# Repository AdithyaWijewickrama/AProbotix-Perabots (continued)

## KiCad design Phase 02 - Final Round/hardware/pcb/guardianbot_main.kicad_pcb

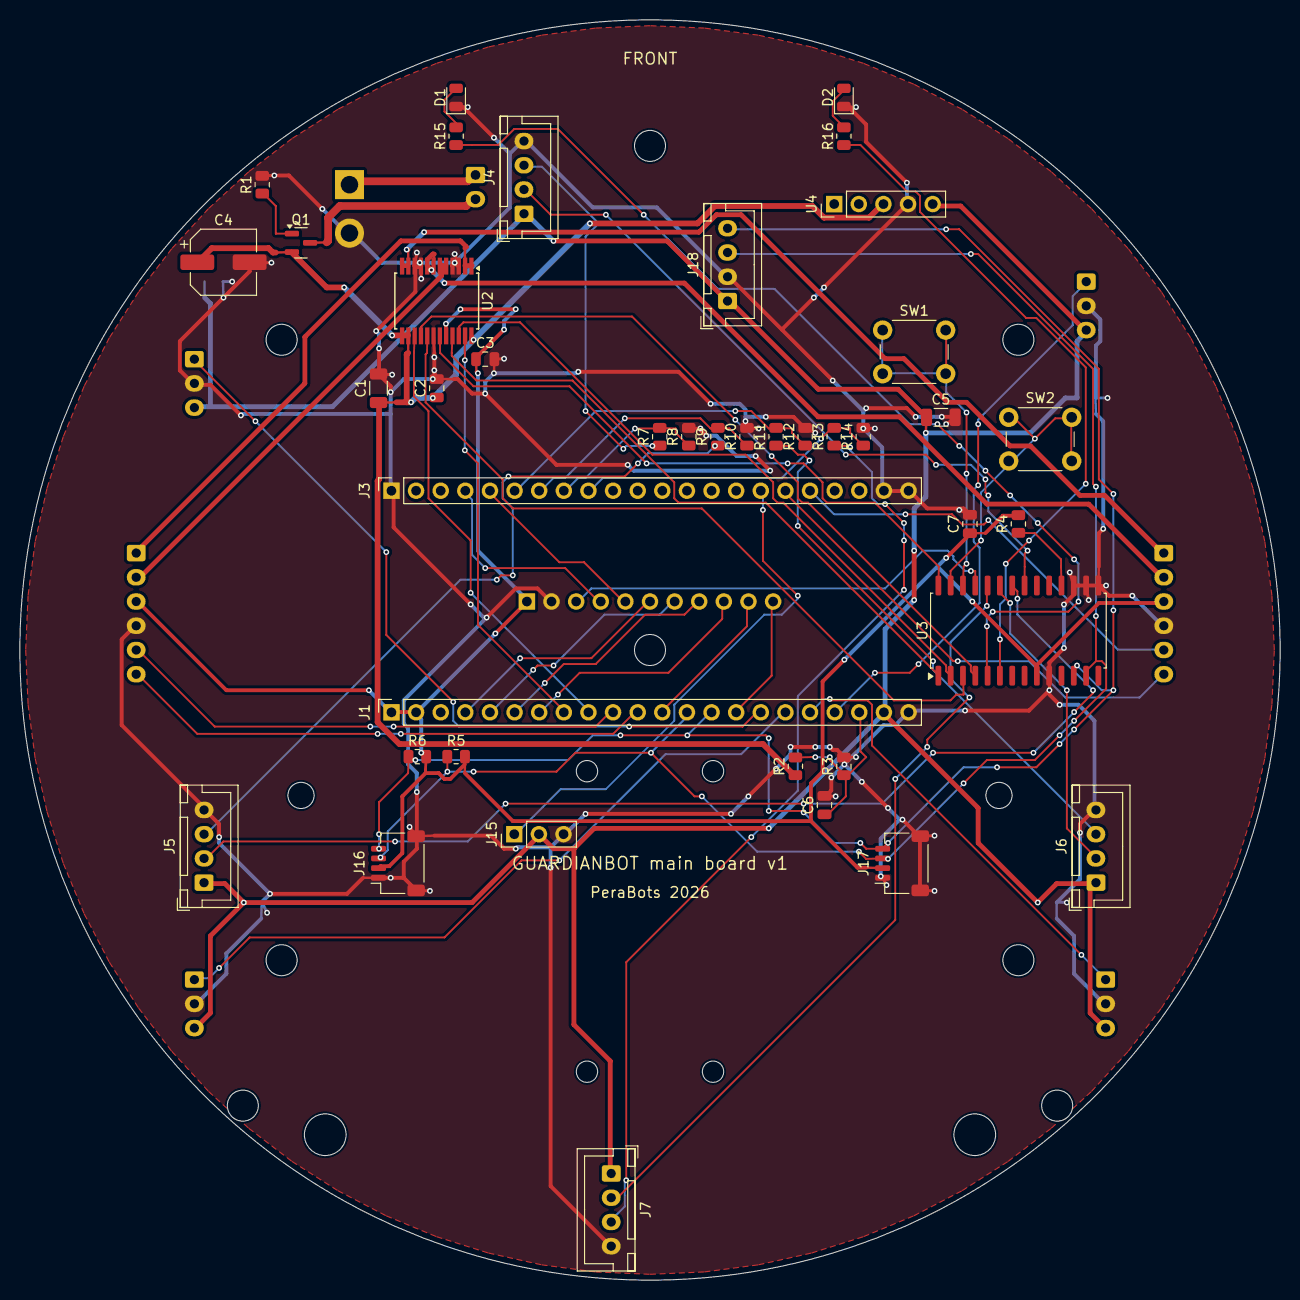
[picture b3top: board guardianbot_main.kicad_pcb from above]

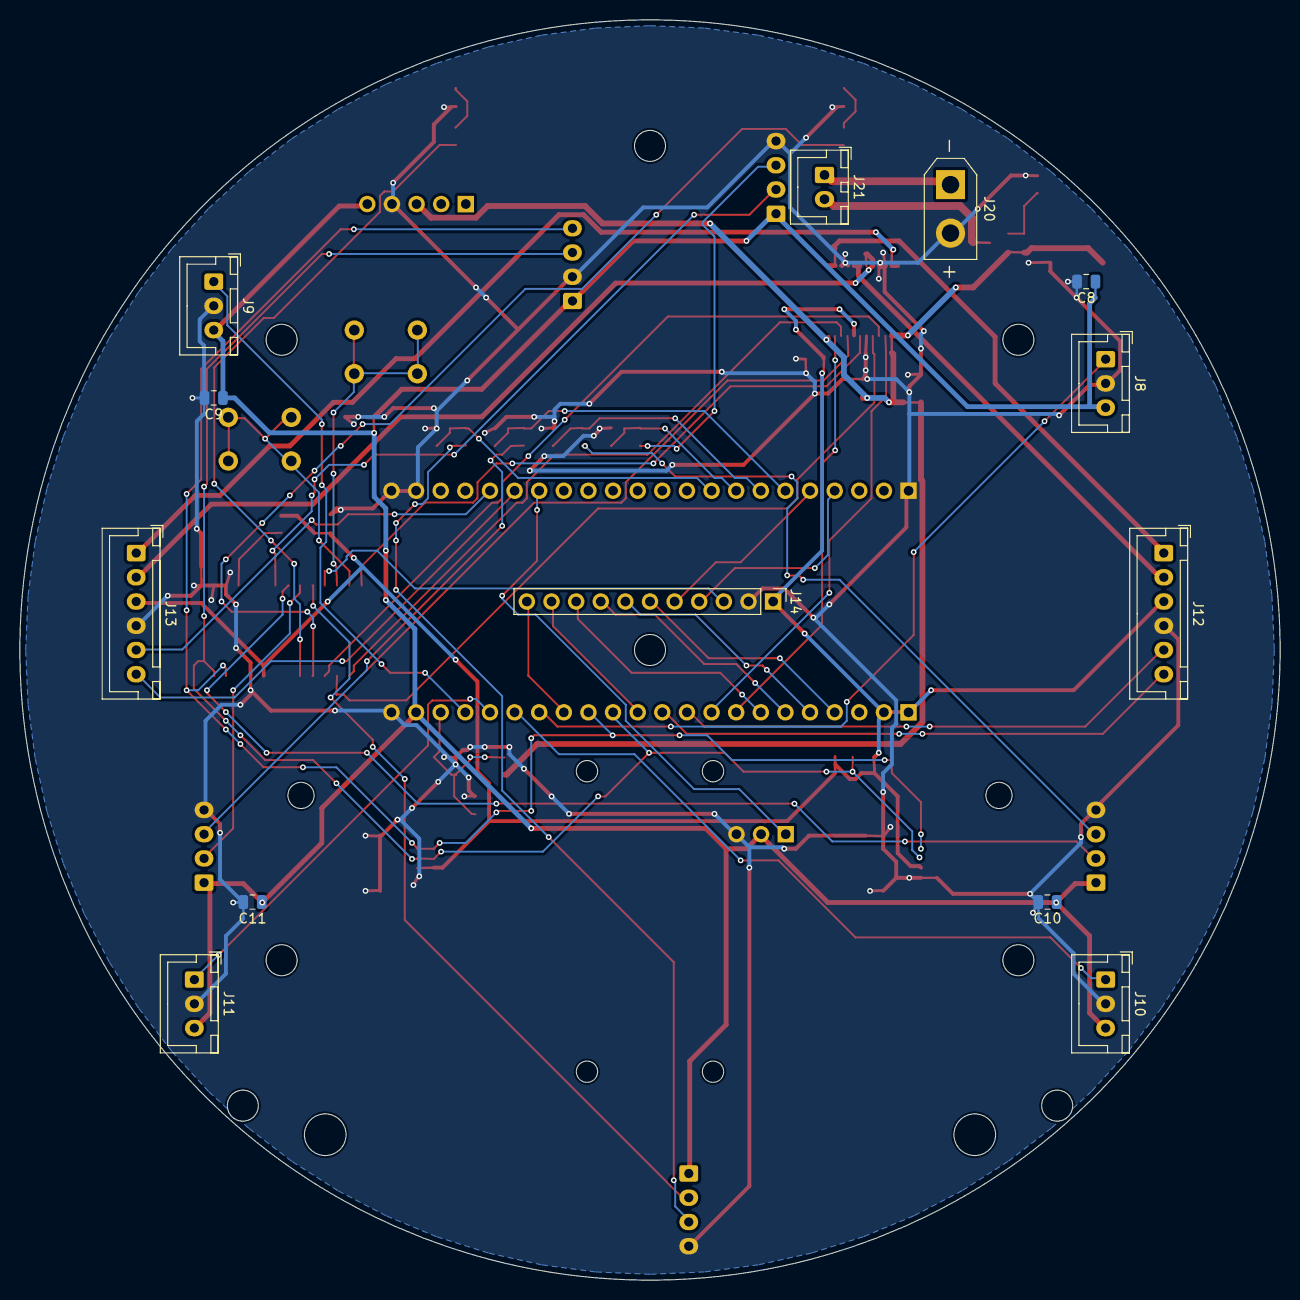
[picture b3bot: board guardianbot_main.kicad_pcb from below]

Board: 2 copper layers, 130.0 x 130.0 mm, 70 parts (13 on the bottom side), 58 nets.

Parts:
C1: 10uF 25V; C_1206_3216Metric
C2, C3, C6, C7: 100nF; C_0805_2012Metric
C4: 220uF 16V; CP_Elec_6.3x7.7
C5: 47uF 10V; C_1206_3216Metric
C8, C9, C10, C11: 10uF; C_0805_2012Metric
D1: BLUE; LED_0805_2012Metric
D2: GREEN; LED_0805_2012Metric
H1, H2, H3, H4, H5, H6, H7, H8: MountingHole_3.2mm_M3
H9, H10: MountingHole_4.3mm_M4
H11, H12: MountingHole_2.7mm_M2.5
H13, H14, H15, H16: MountingHole_2.2mm_M2
J1: DevKitC J1; PinSocket_1x22_P2.54mm_Vertical
J3: DevKitC J3; PinSocket_1x22_P2.54mm_Vertical
J4: US front; JST_XH_B4B-XH-A_1x04_P2.50mm_Vertical
J5: US left; JST_XH_B4B-XH-A_1x04_P2.50mm_Vertical
J6: US right; JST_XH_B4B-XH-A_1x04_P2.50mm_Vertical
J7: US back; JST_XH_B4B-XH-A_1x04_P2.50mm_Vertical
J8: IR front-left; JST_XH_B3B-XH-A_1x03_P2.50mm_Vertical
J9: IR front-right; JST_XH_B3B-XH-A_1x03_P2.50mm_Vertical
J10: IR left; JST_XH_B3B-XH-A_1x03_P2.50mm_Vertical
J11: IR right; JST_XH_B3B-XH-A_1x03_P2.50mm_Vertical
J12: Motor L; JST_XH_B6B-XH-A_1x06_P2.50mm_Vertical
J13: Motor R; JST_XH_B6B-XH-A_1x06_P2.50mm_Vertical
J14: Line array; PinHeader_1x11_P2.54mm_Vertical
J15: Servo; PinHeader_1x03_P2.54mm_Vertical
J16: Qwiic IMU; JST_SH_SM04B-SRSS-TB_1x04-1MP_P1.00mm_Horizontal
J17: Qwiic colour; JST_SH_SM04B-SRSS-TB_1x04-1MP_P1.00mm_Horizontal
J18: XIAO cam; JST_XH_B4B-XH-A_1x04_P2.50mm_Vertical
J20: XT30 battery; AMASS_XT30UPB-M_1x02_P5.0mm_Vertical
J21: Power switch; JST_XH_B2B-XH-A_1x02_P2.50mm_Vertical
Q1: AO3401A; SOT-23
R1, R4, R7, R9, R11, R13: 10k; R_0805_2012Metric
R2: 100k; R_0805_2012Metric
R3: 33k; R_0805_2012Metric
R5, R6: 4.7k; R_0805_2012Metric
R8, R10, R12, R14: 20k; R_0805_2012Metric
R15, R16: 330R; R_0805_2012Metric
SW1: START; SW_PUSH_6mm
SW2: CAL; SW_PUSH_6mm
U2: TB6612FNG; SSOP-24_5.3x8.2mm_P0.65mm
U3: MCP23017-E/SO; SOIC-28W_7.5x17.9mm_P1.27mm
U4: Pololu D24V22F5; PinHeader_1x05_P2.54mm_Vertical

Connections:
+3V3: C3.1, C7.1, J1.1, J1.2, J12.3, J13.3, J14.1, J16.2, J17.2, R4.2, R5.2, R6.2, U2.20, U3.9
+5V: C5.1, C8.1, C9.1, C10.1, C11.1, J1.21, J4.1, J5.1, J6.1, J7.1, J8.3, J9.3, J10.3, J11.3, J15.2, J18.1, U4.5
AIN1: U2.21, U3.1
AIN2: U2.22, U3.2
BAT_RAW: J20.1, J21.1
BAT_SW: J21.2, Q1.3
BIN1: U2.17, U3.3
BIN2: U2.16, U3.4
BTN_CAL: SW2.1, SW2.2, U3.27
BTN_START: SW1.1, SW1.2, U3.26
ECHO_B: J3.9, R13.2, R14.1
ECHO_B5: J7.3, R13.1
ECHO_F: J3.8, R7.2, R8.1
ECHO_F5: J4.3, R7.1
ECHO_L: J3.7, R9.2, R10.1
ECHO_L5: J5.3, R9.1
ECHO_R: J3.6, R11.2, R12.1
ECHO_R5: J6.3, R11.1
ENC_LA: J1.10, J12.5
ENC_LB: J1.11, J12.6
ENC_RA: J3.18, J13.5
ENC_RB: J3.17, J13.6
GND: C1.2, C2.2, C3.2, C4.2, C5.2, C6.2, C7.2, C8.2, C9.2, C10.2, C11.2, D1.1, D2.1, J1.22, J3.1, J3.21, J3.22, J4.4, J5.4, J6.4, J7.4, J8.2, J9.2, J10.2, J11.2, J12.4, J13.4, J14.2, J15.3, J16.1, J16.MP, J17.1, J17.MP, J18.2, J20.2, R1.2, R3.2, R8.2, R10.2, R12.2, R14.2, U2.3, U2.4, U2.9, U2.10, U2.18, U3.10, U3.15, U3.16, U3.17, U4.4
GND_G1: Q1.1, R1.1
IR_FL: J1.16, J8.1
IR_FR: J1.19, J9.1
IR_L: J1.17, J10.1
IR_R: J1.18, J11.1
LED_B: R15.1, U3.5
LED_BA: D1.2, R15.2
LED_G: R16.1, U3.6
LED_GA: D2.2, R16.2
LINE1: J3.4, J14.4
LINE2: J3.5, J14.5
LINE3: J1.4, J14.6
LINE4: J1.5, J14.7
LINE5: J1.6, J14.8
LINE6: J1.7, J14.9
LINE7: J1.12, J14.10
LINE8: J1.15, J14.11
LINE_CTRL: J14.3, U3.25
MCP_RST: R4.1, U3.18
MOT_L1: J12.1, U2.1, U2.2
MOT_L2: J12.2, U2.5, U2.6
MOT_R1: J13.1, U2.11, U2.12
MOT_R2: J13.2, U2.7, U2.8
PWMA: J1.8, U2.23
PWMB: J1.9, U2.15
SCL: J1.14, J16.4, J17.4, J18.4, R6.1, U3.12
SDA: J1.13, J16.3, J17.3, J18.3, R5.1, U3.13
SERVO: J3.16, J15.1
STBY: U2.19, U3.28
TRIG_B: J7.2, U3.24
TRIG_F: J4.2, U3.21
TRIG_L: J5.2, U3.22
TRIG_R: J6.2, U3.23
VBAT: C1.1, C2.1, C4.1, Q1.2, R2.1, U2.13, U2.14, U2.24, U4.3
VBAT_SENSE: C6.1, J1.20, R2.2, R3.1

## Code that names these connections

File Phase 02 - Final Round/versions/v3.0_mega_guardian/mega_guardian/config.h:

/*
 * config.h  -  GuardianBot v3  -  pins, geometry and tunables (Arduino Mega 2560)
 * Change things HERE, not in the other tabs.
 */
#ifndef CONFIG_H
#define CONFIG_H

/* ============================== PINS ================================== */
/* L298N motor driver (ENA/ENB must be PWM pins) */
#define PIN_ENA   5      /* left  PWM */
#define PIN_IN1   22
#define PIN_IN2   23
#define PIN_ENB   6      /* right PWM */
#define PIN_IN3   24
#define PIN_IN4   25

/* Quadrature encoders: channel A on external-interrupt pins, B on plain pins */
#define PIN_ENC_LA  2
#define PIN_ENC_LB  4
#define PIN_ENC_RA  3
#define PIN_ENC_RB  7

/* HC-SR04 ultrasonic (trig, echo) : Front, Left, Right, Back */
#define PIN_US_F_TRIG 26
#define PIN_US_F_ECHO 27
#define PIN_US_L_TRIG 28
#define PIN_US_L_ECHO 29
#define PIN_US_R_TRIG 30
#define PIN_US_R_ECHO 31
#define PIN_US_B_TRIG 32
#define PIN_US_B_ECHO 33

/* TCS3200 colour sensor #1 : FLOOR (points down, front of the robot, ~8 mm above floor) */
#define PIN_CF_S0  34
#define PIN_CF_S1  35
#define PIN_CF_S2  36
#define PIN_CF_S3  37
#define PIN_CF_OUT 38
#define PIN_CF_LED 39
/* TCS3200 colour sensor #2 : GRIPPER (in the pocket, looks at the held piece) */
#define PIN_CG_S0  40
#define PIN_CG_S1  41
#define PIN_CG_S2  42
#define PIN_CG_S3  43
#define PIN_CG_OUT 44
#define PIN_CG_LED 45

/* 5-channel TCRT5000 line array, left -> right, analog inputs */
#define PIN_LINE0  A8
#define PIN_LINE1  A9
#define PIN_LINE2  A10
#define PIN_LINE3  A11
#define PIN_LINE4  A12

/* Servos (metal gear, e.g. MG995 / MG996R) */
#define PIN_SERVO_JAW   8
#define PIN_SERVO_LIFT  9

/* UI */
#define PIN_BTN_START 10   /* to GND, internal pull-up */
#define PIN_BTN_CAL   11
#define PIN_LED_BLUE  12
#define PIN_LED_GREEN 13
#define PIN_BUZZER    52

/* Battery sense: 2S LiPo through 100k (top) / 33k (bottom) divider */
#define PIN_VBAT  A0
#define VBAT_DIVIDER  ((100.0 + 33.0) / 33.0)
#define VBAT_LOW      6.8          /* warn below this (2S) */

/* MPU6050 on I2C (SDA 20, SCL 21), AD0 low -> 0x68 */
#define MPU_ADDR 0x68

/* Serial1 (TX1=18, RX1=19) -> ESP32-S3 log bridge (optional).  Serial = USB. */
#define LOG_BAUD 115200

/* ============================ GEOMETRY ================================ */
#define WHEEL_DIAMETER_MM   40.0
#define TRACK_MM            120.0     /* distance between the two wheel centres */
#define COUNTS_PER_REV      300.0     /* 12 CPR magnetic enc. x 50:1 at 2x decoding = 300 (change if different) */
#define MM_PER_COUNT        (3.14159265 * WHEEL_DIAMETER_MM / COUNTS_PER_REV)

/* sensor offsets from the wheel axle centre (mm, +x forward) */
#define US_F_OFFSET_MM      60.0      /* front ultrasonic face ahead of the axle */
#define US_SIDE_OFFSET_MM   60.0      /* side ultrasonic faces from the robot centre line */
#define LINE_OFFSET_MM      55.0      /* line array ahead of the axle */
#define FLOOR_CS_OFFSET_MM  50.0      /* floor colour sensor ahead of the axle */
#define POCKET_OFFSET_MM    75.0      /* centre of a held piece ahead of the axle */
#define ROBOT_HALF_LEN_MM   80.0      /* axle to front-most point */

/* ============================ ARENA =================================== */
/* World frame = rulebook Figure 1, metres -> we use mm. Origin = arena corner
 * nearest the START zone, +x along the 2.44 m side, +y along the 3.66 m side
 * (same frame as the Webots simulation).                                      */
#define S1_START_X_MM   2314
#define S1_START_Y_MM   126
#define S1_START_HEAD   90        /* degrees, +y */
#define S1_GOAL_X_MM    220       /* in front of the maze entrance door */
#define S1_GOAL_Y_MM    1080
#define S1_GRID_MM      100       /* occupancy cell */
#define S1_COLS         25
#define S1_ROWS         13
#define S1_INFLATE      1         /* cells of inflation around an obstacle (robot radius ~75 mm) */

/* Section 2 maze: 9 x 4 cells, 250 mm pitch, entry cell (0,0) reached heading +y */
#define MZ_CELL_MM      250
#define MZ_ENTRY_C      0
#define MZ_ENTRY_R      0
#define MZ_EXIT_C       8
#define MZ_EXIT_R       3
#define MZ_EXIT_HEAD    H_N       /* direction of the exit door out of the exit cell */
#define WALL_SEEN_MM    180       /* ultrasonic < this at cell centre => wall on that side */
#define WALL_CENTRE_MM  119       /* ideal distance robot-centre -> wall  ( (238)/2 ) */
#define FRONT_STOP_MM   (WALL_CENTRE_MM - US_F_OFFSET_MM)   /* front sensor reading when centred in a cell with a wall ahead */

/* Section 3 board, Figure 1 (mm).  Transverse lines x, long lines y.          */
#define B_XT0  500
#define B_XT1  900
#define B_XT2  1300
#define B_XT3  1700
#define B_YL0  2600
#define B_YL1  2900
#define B_YL2  3200
#define B_YL3  3500
#define B_ENTRY_Y       3050      /* the entry/exit line runs along y = 3050 */
#define B_EXIT_JUNC_X   2210      /* T junction after the maze exit */
#define B_COLLECT_X     2006      /* crossing with the collection line */
#define B_COLLECT_LEN   350       /* mm from the crossing to a collection point */
#define B_END_X         130

/* ============================ MOTION ================================== */
#define PWM_MAX         255
#define PWM_MIN_MOVE    60        /* below this the L298N + motor does not move */
#define SPEED_FAST      200
#define SPEED_NORMAL    150
#define SPEED_SLOW      100
#define SPEED_TURN      130
#define KP_HEAD         4.0       /* PWM per degree of heading error while driving straight */
#define KP_WALL         0.8       /* PWM per mm of wall-centring error (maze) */
#define KP_LINE         35.0      /* PWM per unit of line position error (-2..2) */
#define TURN_TOL_DEG    2.0
#define KP_TURN         3.5
#define TURN_MIN_PWM    85

/* ============================ SENSORS ================================= */
#define US_TIMEOUT_US   12000     /* ~2 m */
#define US_MAX_MM       2000
#define LINE_THRESH     500       /* analog: > this = black (overwritten by calibration) */
#define TCS_READ_MS     40        /* time per channel read */
#define NO_PROGRESS_MS  12000     /* rulebook stops us after 15 s of no progress -> self-recover before */

/* ============================ GRIPPER ================================= */
#define JAW_OPEN_DEG    120
#define JAW_CLOSED_DEG  35
#define LIFT_DOWN_DEG   20
#define LIFT_UP_DEG     70

/* ============================ EEPROM ================================== */
#define EE_MAGIC        0x5A
#define EE_ADDR_MAGIC   0
#define EE_ADDR_CLUES   1        /* 4 bytes: blue, green, right, left */
#define EE_ADDR_CAL     8        /* calibration block */

/* TCS3200 calibration record (white reference + chroma thresholds), stored in EEPROM */
struct ColourCal { float whiteR, whiteG, whiteB; float blueScore, greenScore; };

#endif

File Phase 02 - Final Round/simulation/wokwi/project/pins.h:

// GuardianBot v4.1 - Arduino Mega 2560 pin map (the "body": all real-time I/O)
// The Mega sits upside-down on the PCB mid deck (hardware/pcb_v4). Keep in sync with docs/GuardianBot_v4.1_build_guide.md
#pragma once
#include <stdint.h>

// ---- Pololu DRV8833 carrier (VIN = 2S LiPo, 7.4-8.4 V). PWM on the IN pins at 31 kHz.
#define PIN_AIN1       5    // left motor  (Timer3)
#define PIN_AIN2       6    //             (Timer4)
#define PIN_BIN1       7    // right motor (Timer4)
#define PIN_BIN2       8    //             (Timer4)
#define PIN_DRV_SLEEP  4    // nSLEEP: HIGH = driver on (LOW while the brain is silent)

// ---- N20 hall encoders (x4 quadrature, all four on external interrupts)
#define PIN_ENC_L_A    2    // INT4
#define PIN_ENC_L_B    3    // INT5
#define PIN_ENC_R_A   18    // INT3
#define PIN_ENC_R_B   19    // INT2

// ---- I2C bus (SDA 20, SCL 21): L3G4200D gyro 0x69, 8 x VL53L0X (re-addressed 0x30..0x37), OLED 0x3C

// ---- VL53L0X XSHUT lines. Open-drain use only: pinMode INPUT = sensor on (module pull-up),
//      OUTPUT LOW = sensor off. Never drive HIGH: the XSHUT pin is not 5 V tolerant.
//      order: front, fl, fr, lf, lr, rf, rr, back
static const uint8_t PIN_XSHUT[8] = {30, 31, 32, 33, 34, 35, 36, 37};

// ---- Pololu QTR-8RC on PORTA (D22..D29 = PA0..PA7; sensor 1 = right-most) + emitter control
#define PIN_QTR_LEDON 38

// ---- link to the ESP32-S3 brain: Serial2. TX2 16 -> 1k8/3k3 divider -> S3 GPIO41 (RX),
//      RX2 17 <- 2N7000 shifter <- S3 GPIO42 (TX). Both on the PCB (socket J18, silkscreen "ESP32CAM" from v4.0).
#define LINK_BAUD 250000UL

// ---- 2 x HC-SR04: trig on plain outputs, echo on PCINT0 pins (non-blocking)
#define PIN_US_F_TRIG 39
#define PIN_US_B_TRIG 40
#define PIN_US_F_ECHO 10    // PB4 / PCINT4
#define PIN_US_B_ECHO 11    // PB5 / PCINT5

// ---- 2 x TCS3200 (GY-31). S0 -> 5 V, S1 -> GND on both boards (20 % output scale). S2/S3 shared.
#define PIN_TCS_S2    41
#define PIN_TCS_S3    42
#define PIN_TCS_FLOOR_OUT 50  // PB3 / PCINT3
#define PIN_TCS_FRONT_OUT 51  // PB2 / PCINT2
#define PIN_TCS_FLOOR_LED 43
#define PIN_TCS_FRONT_LED 44

// ---- gripper servos (Kpower M0170 on the 5.5 V servo rail)
#define PIN_SERVO_L   45
#define PIN_SERVO_R   46

// ---- 1x4 membrane keypad (common -> GND, internal pull-ups)
//      K1 START   K2 start at the maze entrance   K3 Section 3 restart   K4 CAL (white balance)
static const uint8_t PIN_KEY[4] = {47, 48, 49, 53};

// ---- clan LEDs, buzzer, battery
#define PIN_LED_BLUE  A1
#define PIN_LED_GREEN A2
#define PIN_BUZZER     9    // active buzzer via NPN
#define PIN_VBAT      A0    // 20k / 10k divider from the switched battery (8.4 V -> 2.8 V)
